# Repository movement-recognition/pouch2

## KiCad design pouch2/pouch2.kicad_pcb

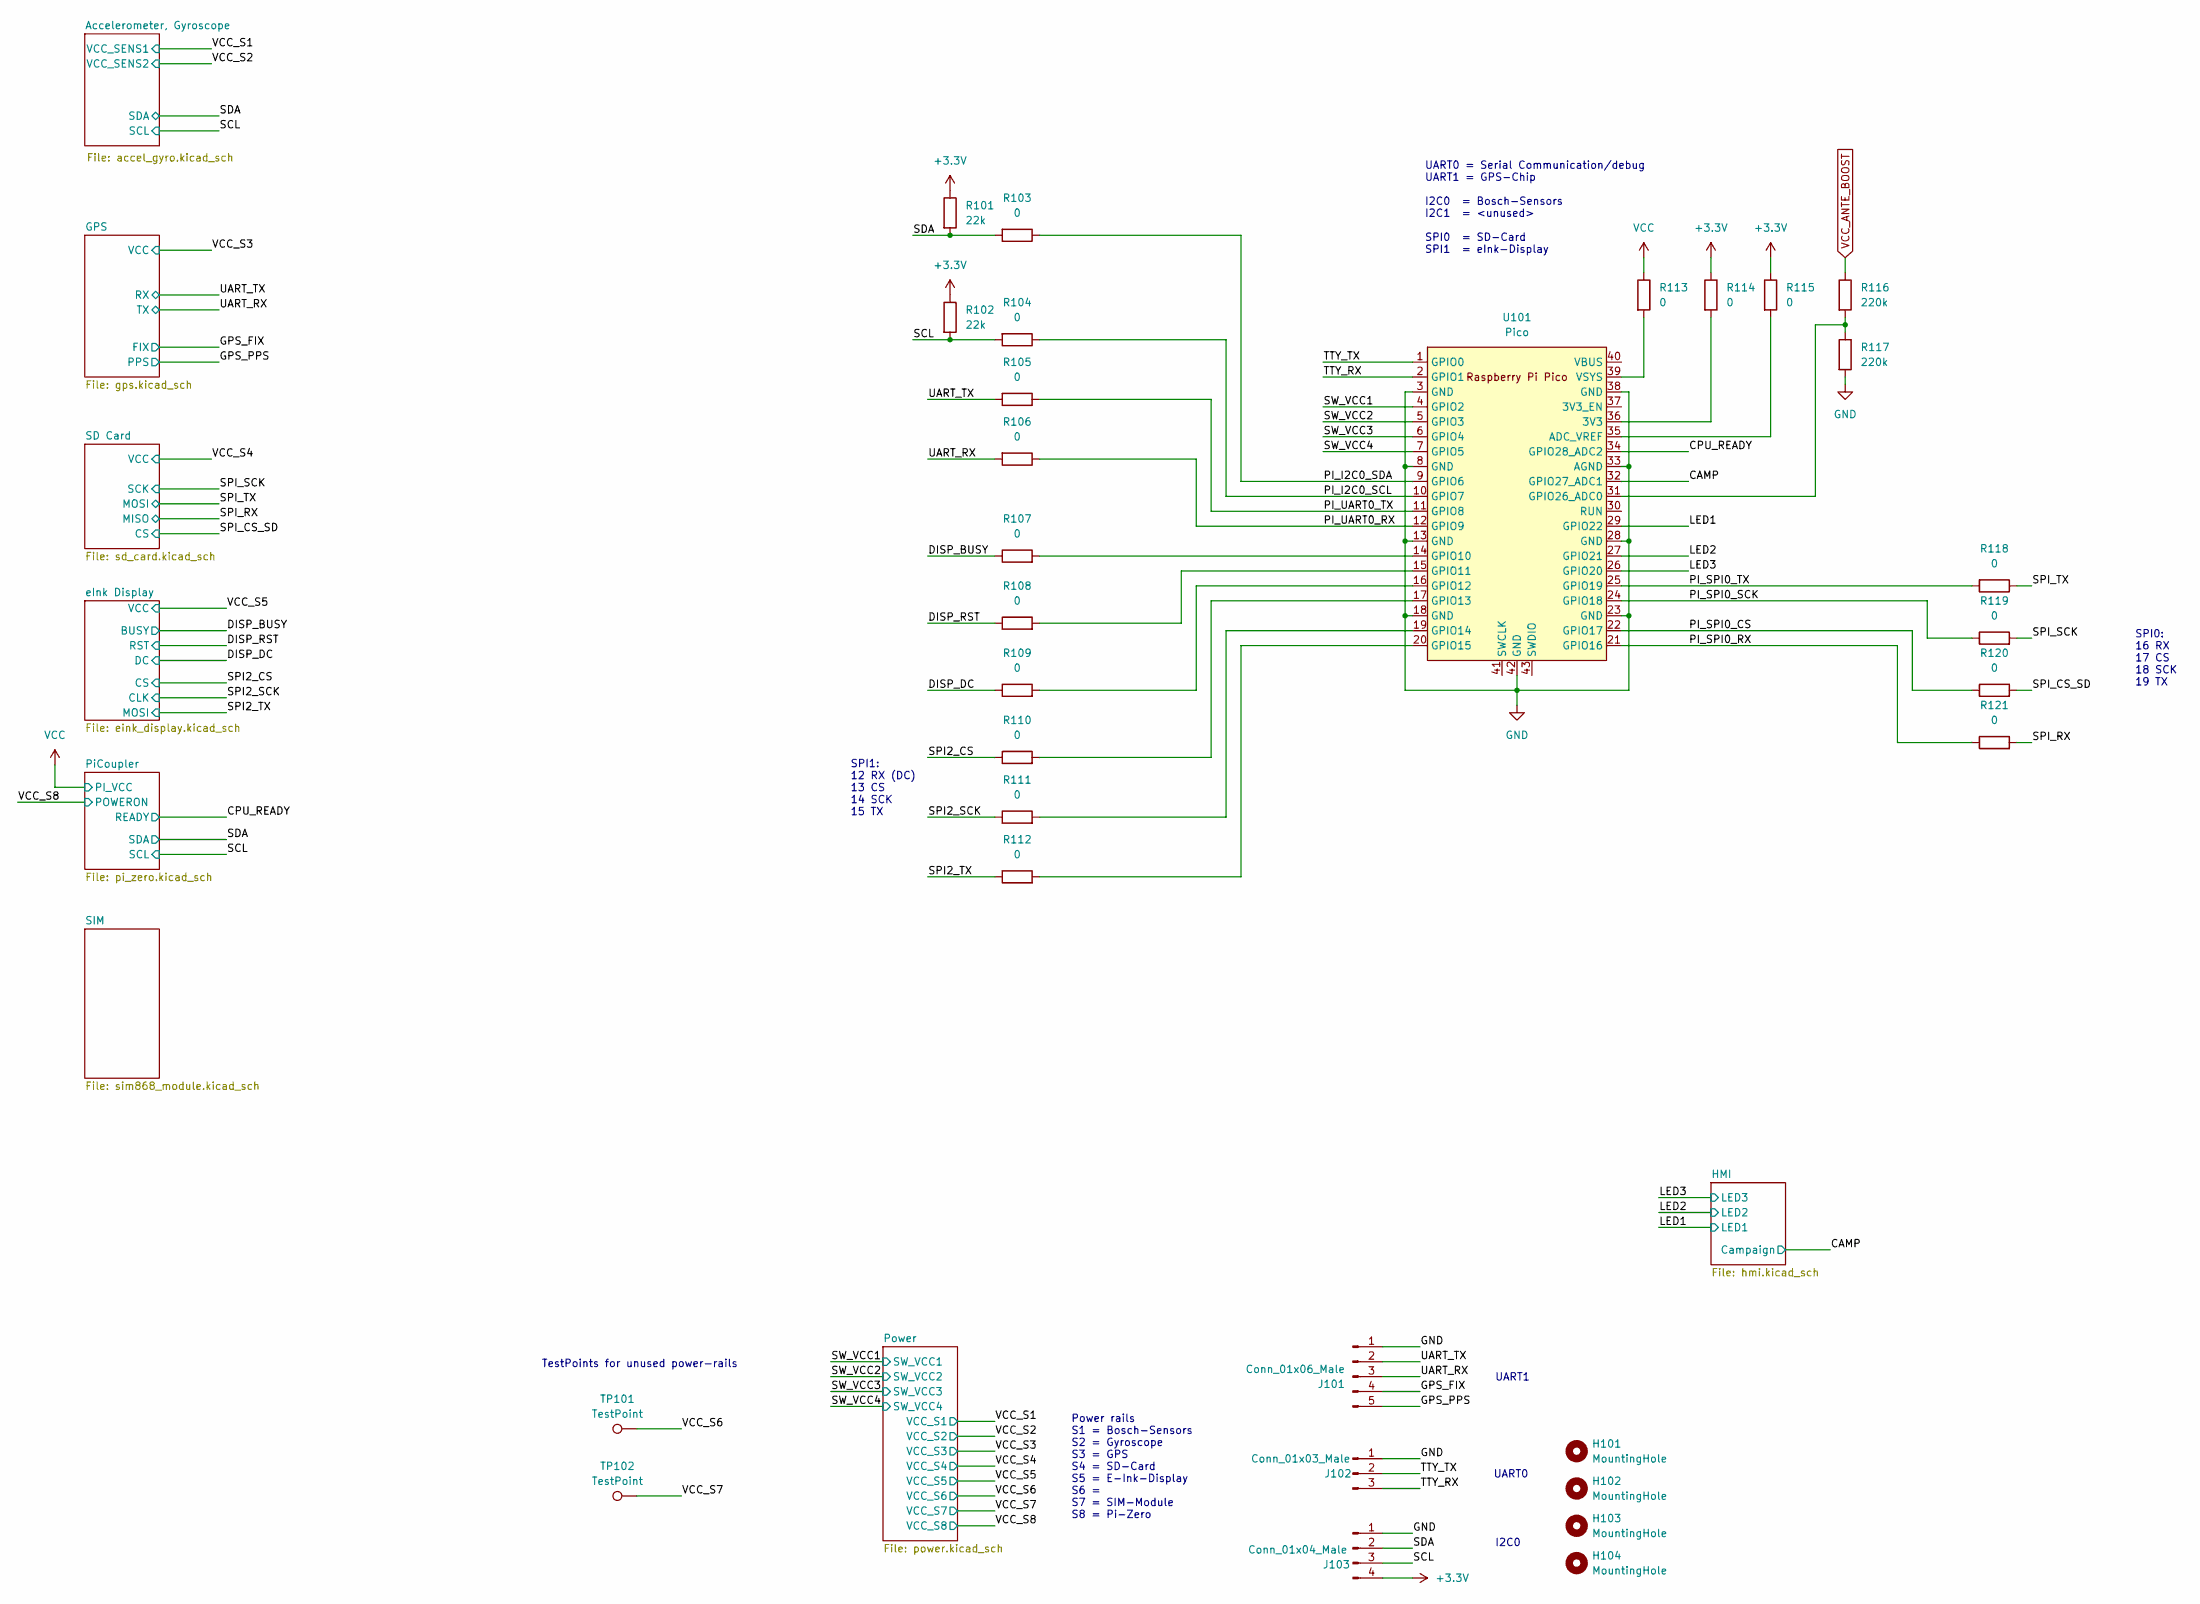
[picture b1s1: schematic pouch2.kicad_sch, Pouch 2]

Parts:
H101, H102, H103, H104: MountingHole; MountingHole_3.2mm_M3_DIN965_Pad_TopBottom
J101: Conn_01x06_Male; PinHeader_1x05_P2.54mm_Vertical
J102: Conn_01x03_Male; PinHeader_1x03_P2.54mm_Vertical
J103: Conn_01x04_Male; PinHeader_1x04_P2.54mm_Vertical
R101, R102: 22k; R_0805_2012Metric; MPN_Eurocircuit GPR080522K; LCSC C17560
R103, R104, R105, R106, R107, R108, R109, R110, R111, R112, R113, R114, R115, R118, R119, R120, R121: 0; R_0805_2012Metric; MPN_Eurocircuit GPR08050R; LCSC C17477
R116, R117: 220k; R_0805_2012Metric; MPN_Eurocircuit GPR0805220K; LCSC C17556
TP101, TP102: TestPoint; TestPoint_Pad_1.0x1.0mm
U101: Pico; RPi_Pico_SMD_TH

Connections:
+3.3V: J103.4, R101.1, R102.1, R114.1, R115.1; also elsewhere on the board
/CAMP: U101.32 (GPIO27_ADC1); also elsewhere on the board
/CPU_READY: U101.34 (GPIO28_ADC2); also elsewhere on the board
/DISP_BUSY: R107.1; also elsewhere on the board
/DISP_DC: R109.1; also elsewhere on the board
/DISP_RST: R108.1; also elsewhere on the board
/GPS_FIX: J101.4; also elsewhere on the board
/GPS_PPS: J101.5; also elsewhere on the board
/LED1: U101.29 (GPIO22); also elsewhere on the board
/LED2: U101.27 (GPIO21); also elsewhere on the board
/LED3: U101.26 (GPIO20); also elsewhere on the board
/PI_I2C0_SCL: R104.1, U101.10 (GPIO7)
/PI_I2C0_SDA: R103.1, U101.9 (GPIO6)
/PI_SPI0_CS: R120.1, U101.22 (GPIO17)
/PI_SPI0_RX: R121.1, U101.21 (GPIO16)
/PI_SPI0_SCK: R119.1, U101.24 (GPIO18)
/PI_SPI0_TX: R118.2, U101.25 (GPIO19)
/PI_UART0_RX: R106.1, U101.12 (GPIO9)
/PI_UART0_TX: R105.1, U101.11 (GPIO8)
/SCL: J103.3, R102.2, R104.2; also elsewhere on the board
/SDA: J103.2, R101.2, R103.2; also elsewhere on the board
/SPI2_CS: R110.1; also elsewhere on the board
/SPI2_SCK: R111.1; also elsewhere on the board
/SPI2_TX: R112.1; also elsewhere on the board
/SPI_CS_SD: R120.2; also elsewhere on the board
/SPI_RX: R121.2; also elsewhere on the board
/SPI_SCK: R119.2; also elsewhere on the board
/SPI_TX: R118.1; also elsewhere on the board
/SW_VCC1: U101.4 (GPIO2); also elsewhere on the board
/SW_VCC2: U101.5 (GPIO3); also elsewhere on the board
/SW_VCC3: U101.6 (GPIO4); also elsewhere on the board
/SW_VCC4: U101.7 (GPIO5); also elsewhere on the board
/TTY_RX: J102.3, U101.2 (GPIO1)
/TTY_TX: J102.2, U101.1 (GPIO0)
/UART_RX: J101.3, R106.2; also elsewhere on the board
/UART_TX: J101.2, R105.2; also elsewhere on the board
/VCC_S6: TP101.1; also elsewhere on the board
/VCC_S7: TP102.1; also elsewhere on the board
GND: J101.1, J102.1, J103.1, R117.2, U101.3 (GND), U101.8 (GND), U101.13 (GND), U101.18 (GND), U101.23 (GND), U101.28 (GND), U101.33 (AGND), U101.38 (GND), U101.42 (GND); also elsewhere on the board
unnamed: R114.2, U101.36 (3V3)
unnamed: R115.2, U101.35 (ADC_VREF)
unnamed: R107.2, U101.14 (GPIO10)
unnamed: R108.2, U101.15 (GPIO11)
unnamed: R109.2, U101.16 (GPIO12)
unnamed: R110.2, U101.17 (GPIO13)
unnamed: R111.2, U101.19 (GPIO14)
unnamed: R112.2, U101.20 (GPIO15)
unnamed: R116.2, R117.1, U101.31 (GPIO26_ADC0)
unnamed: R113.2, U101.39 (VSYS)
VCC: R113.1; also elsewhere on the board
VCC_ANTE_BOOST: R116.1; also elsewhere on the board

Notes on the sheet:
UART1
Power rails S1 = Bosch-Sensors S2 = Gyroscope S3 = GPS S4 = SD-Card S5 = E-Ink-Display S6 = S7 = SIM-Module S8 = Pi-Zero
UART0
SPI0: 16 RX 17 CS 18 SCK 19 TX
TestPoints for unused power-rails
SPI1: 12 RX (DC) 13 CS 14 SCK 15 TX
I2C0
UART0 = Serial Communication/debug UART1 = GPS-Chip I2C0 = Bosch-Sensors I2C1 = <unused> SPI0 = SD-Card SPI1 = eInk-Display

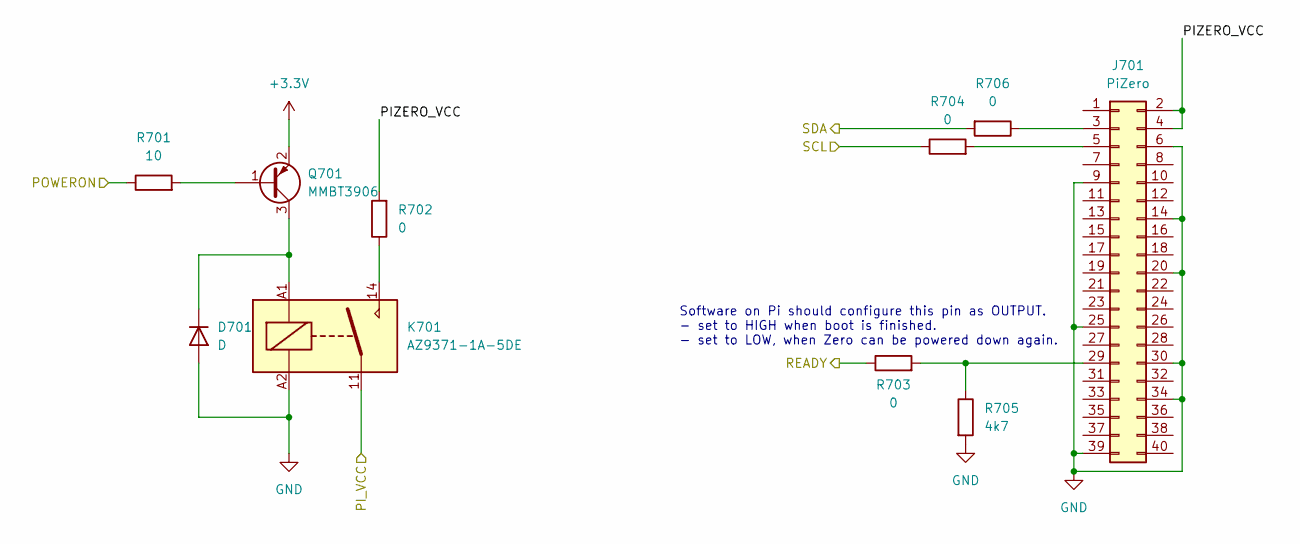
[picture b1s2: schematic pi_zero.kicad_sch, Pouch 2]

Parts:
D701: D; D_0805_2012Metric
J701: PiZero; Raspberry_Pi_Zero_Socket_wo_drills
K701: AZ9371-1A-5DE; Relay_1-Form-A_Schrack-RYII_RM5mm
Q701: MMBT3906; SOT-23; MPN_Eurocircuit MMBT3906
R701: 10; R_0805_2012Metric; MPN_Eurocircuit GPR080510R; LCSC C17415
R702, R703, R704, R706: 0; R_0805_2012Metric; MPN_Eurocircuit GPR08050R; LCSC C17477
R705: 4k7; R_0805_2012Metric; MPN_Eurocircuit GPR08054K7; LCSC C17673

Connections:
+3.3V: Q701.2 (E); also elsewhere on the board
/CPU_READY: R703.1; also elsewhere on the board
/PiCoupler/PIZERO_VCC: J701.2, J701.4, R702.2
/SCL: R704.1; also elsewhere on the board
/SDA: R706.2; also elsewhere on the board
/VCC_S8: R701.1; also elsewhere on the board
GND: D701.2 (A), J701.6, J701.9, J701.14, J701.20, J701.25, J701.30, J701.34, J701.39, K701.A2, R705.2; also elsewhere on the board
unnamed: D701.1 (K), K701.A1, Q701.3 (C)
unnamed: J701.3, R706.1
unnamed: J701.5, R704.2
unnamed: J701.29, R703.2, R705.1
unnamed: K701.14, R702.1
unnamed: Q701.1 (B), R701.2
VCC: K701.11; also elsewhere on the board

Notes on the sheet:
Software on Pi should configure this pin as OUTPUT. - set to HIGH when boot is finished. - set to LOW, when Zero can be powered down again.

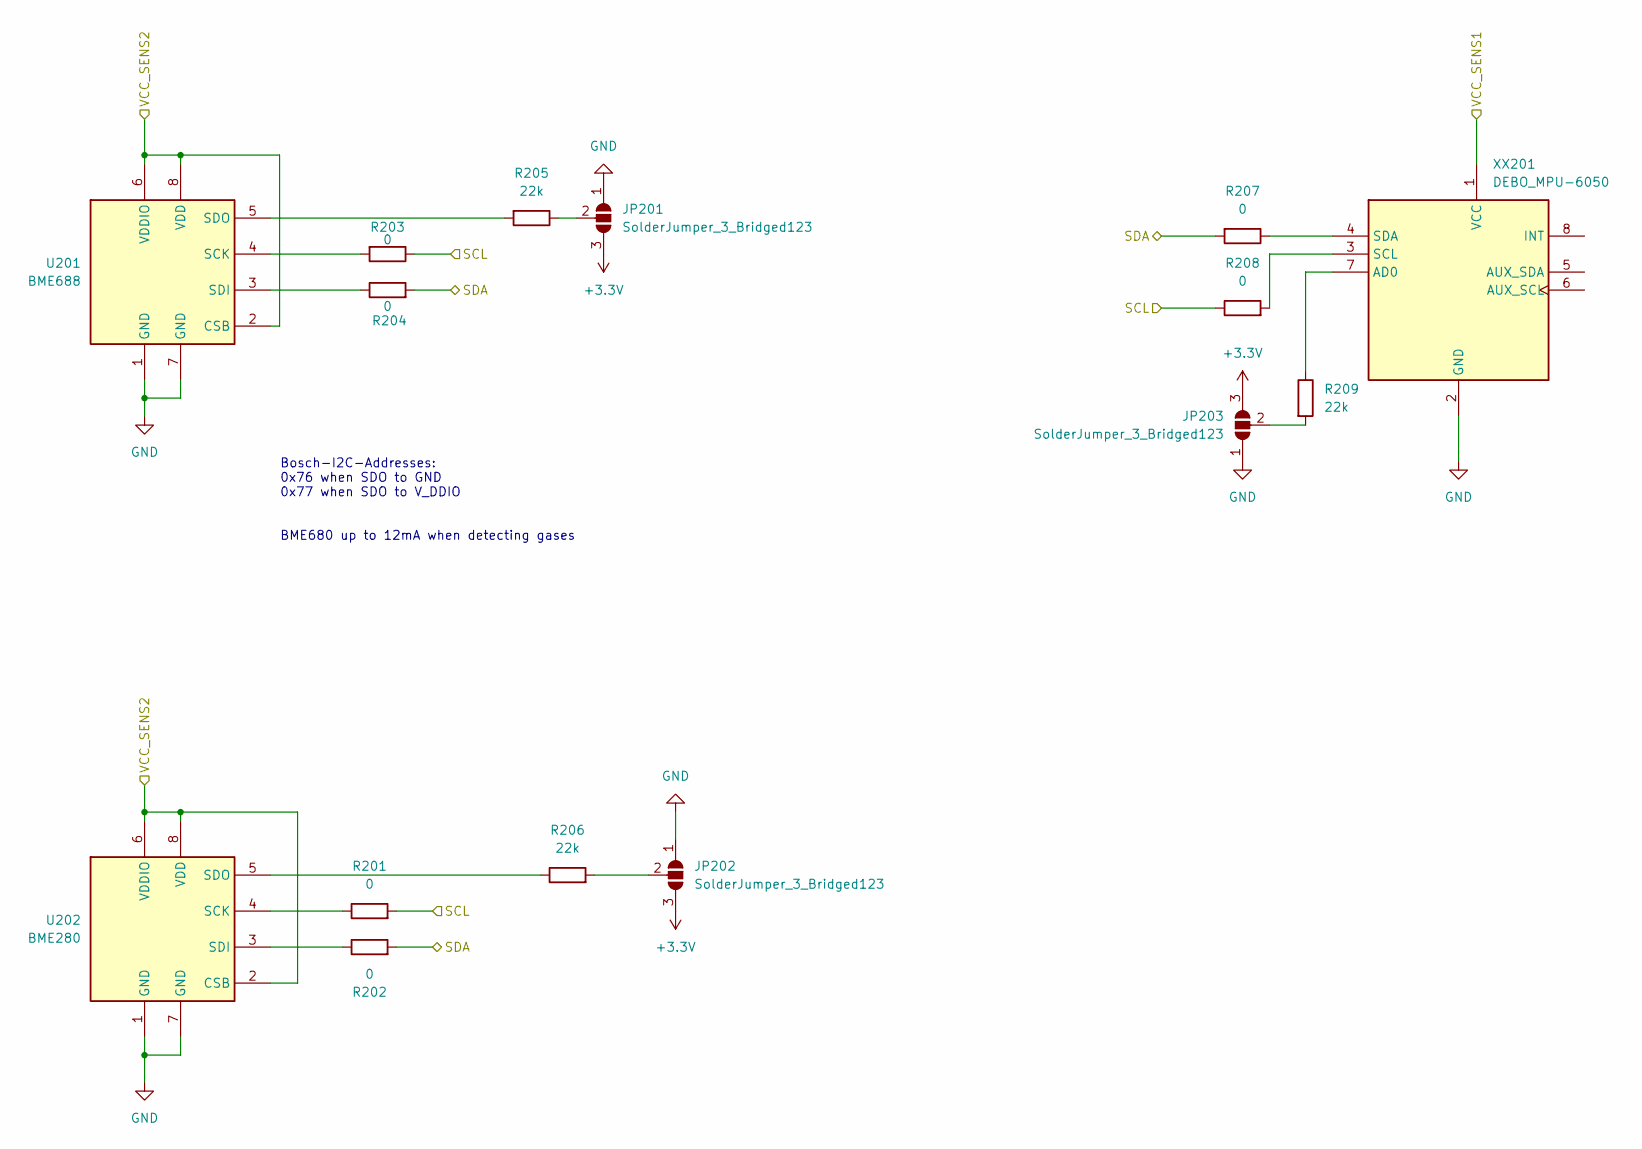
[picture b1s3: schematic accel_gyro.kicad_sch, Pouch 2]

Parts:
JP201, JP202, JP203: SolderJumper_3_Bridged123; SolderJumper-3_P2.0mm_Open_TrianglePad1.0x1.5mm_NumberLabels
R201, R202, R203, R204, R207, R208: 0; R_0805_2012Metric; MPN_Eurocircuit GPR08050R; LCSC C17477
R205, R206, R209: 22k; R_0805_2012Metric; MPN_Eurocircuit GPR080522K; LCSC C17560
U201: BME688; Bosch_LGA-8_3x3mm_P0.8mm_ClockwisePinNumbering
U202: BME280; Bosch_LGA-8_2.5x2.5mm_P0.65mm_ClockwisePinNumbering
XX201: DEBO_MPU-6050; DEBO_MPU6050

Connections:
+3.3V: JP201.3 (B), JP202.3 (B), JP203.3 (B); also elsewhere on the board
/SCL: R201.2, R203.1, R208.1; also elsewhere on the board
/SDA: R202.2, R204.2, R207.2; also elsewhere on the board
/VCC_S1: XX201.1 (VCC); also elsewhere on the board
/VCC_S2: U201.2 (CSB), U201.6 (VDDIO), U201.8 (VDD), U202.2 (CSB), U202.6 (VDDIO), U202.8 (VDD); also elsewhere on the board
GND: JP201.1 (A), JP202.1 (A), JP203.1 (A), U201.1 (GND), U201.7 (GND), U202.1 (GND), U202.7 (GND), XX201.2 (GND); also elsewhere on the board
unnamed: JP201.2 (C), R205.1
unnamed: JP202.2 (C), R206.2
unnamed: JP203.2 (C), R209.2
unnamed: R203.2, U201.4 (SCK)
unnamed: R204.1, U201.3 (SDI)
unnamed: R205.2, U201.5 (SDO)
unnamed: R201.1, U202.4 (SCK)
unnamed: R202.1, U202.3 (SDI)
unnamed: R206.1, U202.5 (SDO)
unnamed: R209.1, XX201.7 (AD0)
unnamed: R208.2, XX201.3 (SCL)
unnamed: R207.1, XX201.4 (SDA)

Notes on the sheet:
Bosch-I2C-Addresses: 0x76 when SDO to GND 0x77 when SDO to V_DDIO BME680 up to 12mA when detecting gases

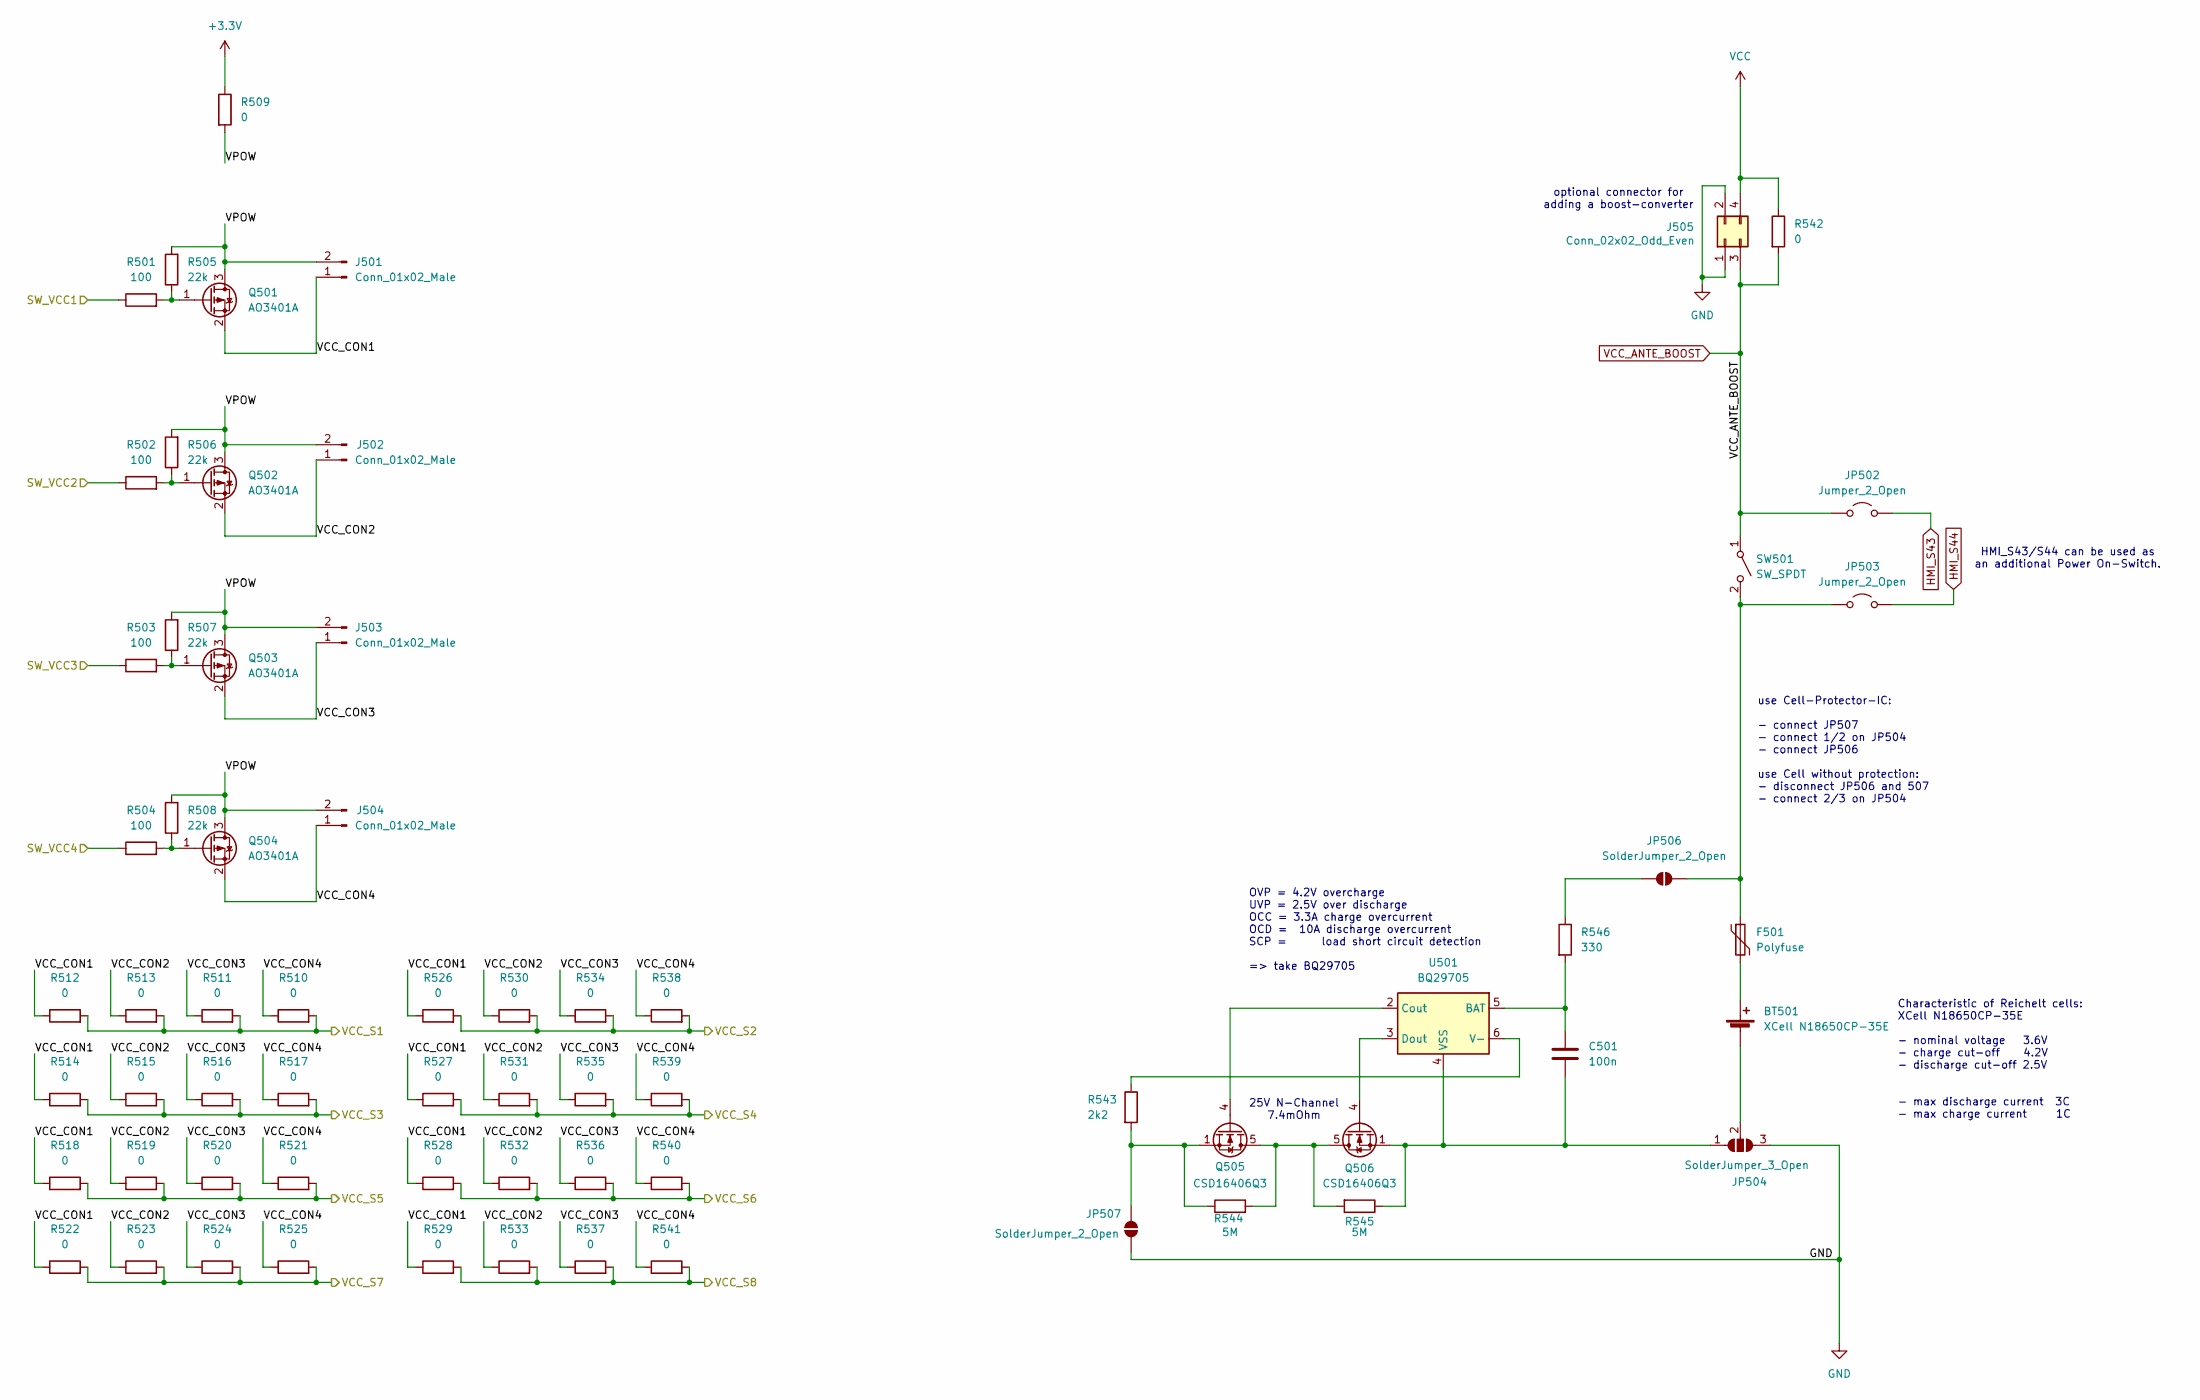
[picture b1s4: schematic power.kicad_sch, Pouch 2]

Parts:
BT501: XCell N18650CP-35E; 18650_Keystone_1043
C501: 100n; C_0805_2012Metric; MPN_Eurocircuit GPC0805104
F501: Polyfuse; Fuse_BelFuse_0ZRE0005FF_L8.3mm_W3.8mm
J501, J502, J503, J504: Conn_01x02_Male; PinHeader_1x02_P2.54mm_Vertical
J505: Conn_02x02_Odd_Even; PinHeader_1x04_P2.54mm_Vertical
JP502, JP503: Jumper_2_Open; SolderJumper-2_P1.3mm_Open_TrianglePad1.0x1.5mm
JP504: SolderJumper_3_Open; SolderJumper-3_P2.0mm_Open_TrianglePad1.0x1.5mm_NumberLabels
JP506, JP507: SolderJumper_2_Open; SolderJumper-2_P1.3mm_Open_TrianglePad1.0x1.5mm
Q501, Q502, Q503, Q504: AO3401A; SOT-23; MPN_Eurocircuit AO3401A; LCSC C15127
Q505, Q506: CSD16406Q3; VSON-8-1EP_3x3mm_P0.65mm_EP1.65x2.4mm; MPN_Eurocircuit CSD16406Q3
R501, R502, R503, R504: 100; R_0805_2012Metric; MPN_Eurocircuit GPR0805100R; LCSC C17408
R505, R506, R507, R508: 22k; R_0805_2012Metric; MPN_Eurocircuit GPR080522K; LCSC C17560
R509, R510, R511, R512, R513, R514, R515, R516, R517, R518, R519, R520, R521, R522, R523, R524, R525, R526, R527, R528, R529, R530, R531, R532, R533, R534, R535, R536, R537, R538, R539, R540, R541, R542: 0; R_0805_2012Metric; MPN_Eurocircuit GPR08050R; LCSC C17477
R543: 2k2; R_0805_2012Metric; MPN_Eurocircuit GPR08052K2; LCSC C17520
R544, R545: 5M; R_0805_2012Metric; MPN_Eurocircuit GPR08055M1; LCSC C2933370
R546: 330; R_0805_2012Metric; MPN_Eurocircuit GPR0805330R; LCSC C17630
SW501: SW_SPDT; PinHeader_1x02_P2.54mm_Vertical
U501: BQ29705; WSON-6_1.5x1.5mm_P0.5mm; MPN_Eurocircuit BQ29705DSER

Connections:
+3.3V: R509.1; also elsewhere on the board
/Power/VCC_CON1: J501.1, Q501.2 (S), R512.1, R514.1, R518.1, R522.1, R526.1, R527.1, R528.1, R529.1
/Power/VCC_CON2: J502.1, Q502.2 (S), R513.1, R515.1, R519.1, R523.1, R530.1, R531.1, R532.1, R533.1
/Power/VCC_CON3: J503.1, Q503.2 (S), R511.1, R516.1, R520.1, R524.1, R534.1, R535.1, R536.1, R537.1
/Power/VCC_CON4: J504.1, Q504.2 (S), R510.1, R517.1, R521.1, R525.1, R538.1, R539.1, R540.1, R541.1
/Power/VPOW: J501.2, J502.2, J503.2, J504.2, Q501.3 (D), Q502.3 (D), Q503.3 (D), Q504.3 (D), R505.2, R506.2, R507.2, R508.2, R509.2
/SW_VCC1: R501.1; also elsewhere on the board
/SW_VCC2: R502.1; also elsewhere on the board
/SW_VCC3: R503.1; also elsewhere on the board
/SW_VCC4: R504.1; also elsewhere on the board
/VCC_S1: R510.2, R511.2, R512.2, R513.2; also elsewhere on the board
/VCC_S2: R526.2, R530.2, R534.2, R538.2; also elsewhere on the board
/VCC_S3: R514.2, R515.2, R516.2, R517.2; also elsewhere on the board
/VCC_S4: R527.2, R531.2, R535.2, R539.2; also elsewhere on the board
/VCC_S5: R518.2, R519.2, R520.2, R521.2; also elsewhere on the board
/VCC_S6: R528.2, R532.2, R536.2, R540.2; also elsewhere on the board
/VCC_S7: R522.2, R523.2, R524.2, R525.2; also elsewhere on the board
/VCC_S8: R529.2, R533.2, R537.2, R541.2; also elsewhere on the board
GND: J505.1, J505.2, JP504.3 (B), JP507.1 (A); also elsewhere on the board
HMI_S43: JP502.2 (B); also elsewhere on the board
HMI_S44: JP503.2 (B); also elsewhere on the board
unnamed: BT501.1 (+), F501.2
unnamed: BT501.2 (-), JP504.2 (C)
unnamed: F501.1, JP503.1 (A), JP506.1 (A), SW501.2 (B)
unnamed: C501.2, JP504.1 (A), Q506.1 (S), Q506.2 (S), Q506.3 (S), R545.1, U501.4 (VSS)
unnamed: JP506.2 (B), R546.1
unnamed: JP507.2 (B), Q505.1 (S), Q505.2 (S), Q505.3 (S), R543.2, R544.1
unnamed: Q501.1 (G), R501.2, R505.1
unnamed: Q502.1 (G), R502.2, R506.1
unnamed: Q503.1 (G), R503.2, R507.1
unnamed: Q504.1 (G), R504.2, R508.1
unnamed: Q505.5 (D), Q506.5 (D), R544.2, R545.2
unnamed: Q505.4 (G), U501.2 (Cout)
unnamed: Q506.4 (G), U501.3 (Dout)
unnamed: C501.1, R546.2, U501.5 (BAT)
unnamed: R543.1, U501.6 (V-)
VCC: J505.4, R542.1; also elsewhere on the board
VCC_ANTE_BOOST: J505.3, JP502.1 (A), R542.2, SW501.1 (A); also elsewhere on the board

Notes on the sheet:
25V N-Channel 7.4mOhm
HMI_S43/S44 can be used as an additional Power On-Switch.
OVP = 4.2V overcharge UVP = 2.5V over discharge OCC = 3.3A charge overcurrent OCD = 10A discharge overcurrent SCP = load short circuit detection => take BQ29705
use Cell-Protector-IC: - connect JP507 - connect 1/2 on JP504 - connect JP506 use Cell without protection: - disconnect JP506 and 507 - connect 2/3 on JP504
optional connector for adding a boost-converter
Characteristic of Reichelt cells: XCell N18650CP-35E - nominal voltage 3.6V - charge cut-off 4.2V - discharge cut-off 2.5V - max discharge current 3C - max charge current 1C

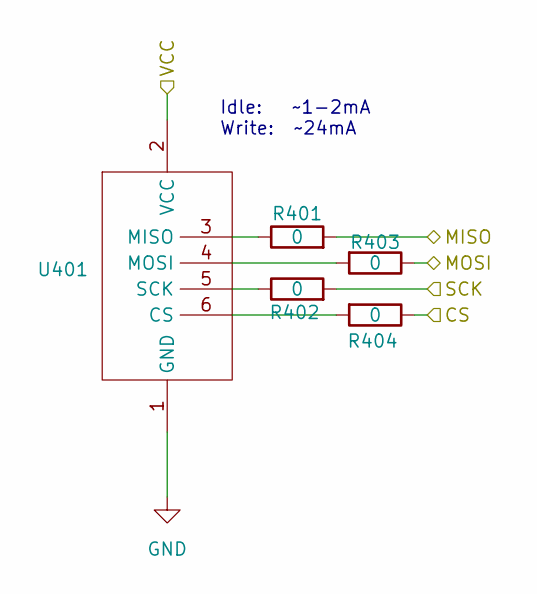
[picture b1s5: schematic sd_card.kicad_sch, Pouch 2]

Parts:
R401, R402, R403, R404: 0; R_0805_2012Metric; MPN_Eurocircuit GPR08050R; LCSC C17477
U401: DEBO_SD-Card

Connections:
/SPI_CS_SD: R404.1; also elsewhere on the board
/SPI_RX: R401.2; also elsewhere on the board
/SPI_SCK: R402.2; also elsewhere on the board
/SPI_TX: R403.1; also elsewhere on the board
/VCC_S4: U401.2 (VCC); also elsewhere on the board
GND: U401.1 (GND); also elsewhere on the board
unnamed: R404.2, U401.6 (CS)
unnamed: R401.1, U401.3 (MISO)
unnamed: R403.2, U401.4 (MOSI)
unnamed: R402.1, U401.5 (SCK)

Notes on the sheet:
Idle: ~1-2mA Write: ~24mA

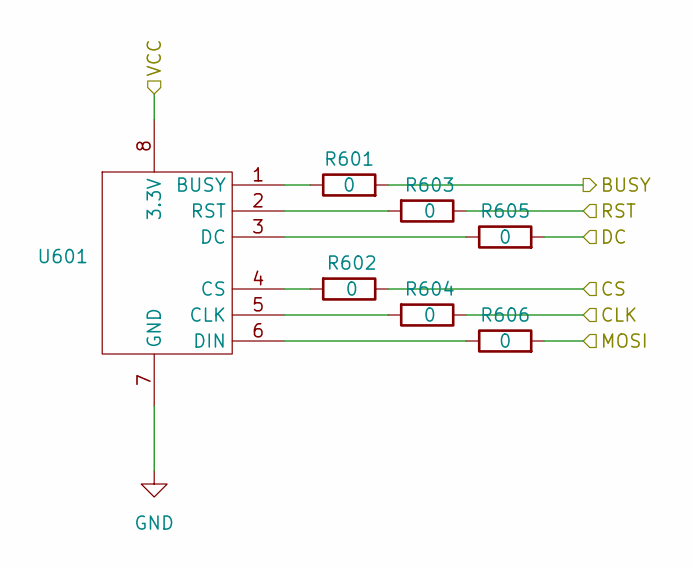
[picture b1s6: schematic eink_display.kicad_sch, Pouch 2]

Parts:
R601, R602, R603, R604, R605, R606: 0; R_0805_2012Metric; MPN_Eurocircuit GPR08050R; LCSC C17477
U601: PinHeader_1x08_P2.54mm_Vertical

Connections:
/DISP_BUSY: R601.2; also elsewhere on the board
/DISP_DC: R605.2; also elsewhere on the board
/DISP_RST: R603.1; also elsewhere on the board
/SPI2_CS: R602.1; also elsewhere on the board
/SPI2_SCK: R604.1; also elsewhere on the board
/SPI2_TX: R606.2; also elsewhere on the board
/VCC_S5: U601.8 (3.3V); also elsewhere on the board
GND: U601.7 (GND); also elsewhere on the board
unnamed: R601.1, U601.1 (BUSY)
unnamed: R604.2, U601.5 (CLK)
unnamed: R602.2, U601.4 (CS)
unnamed: R605.1, U601.3 (DC)
unnamed: R606.1, U601.6 (DIN)
unnamed: R603.2, U601.2 (RST)

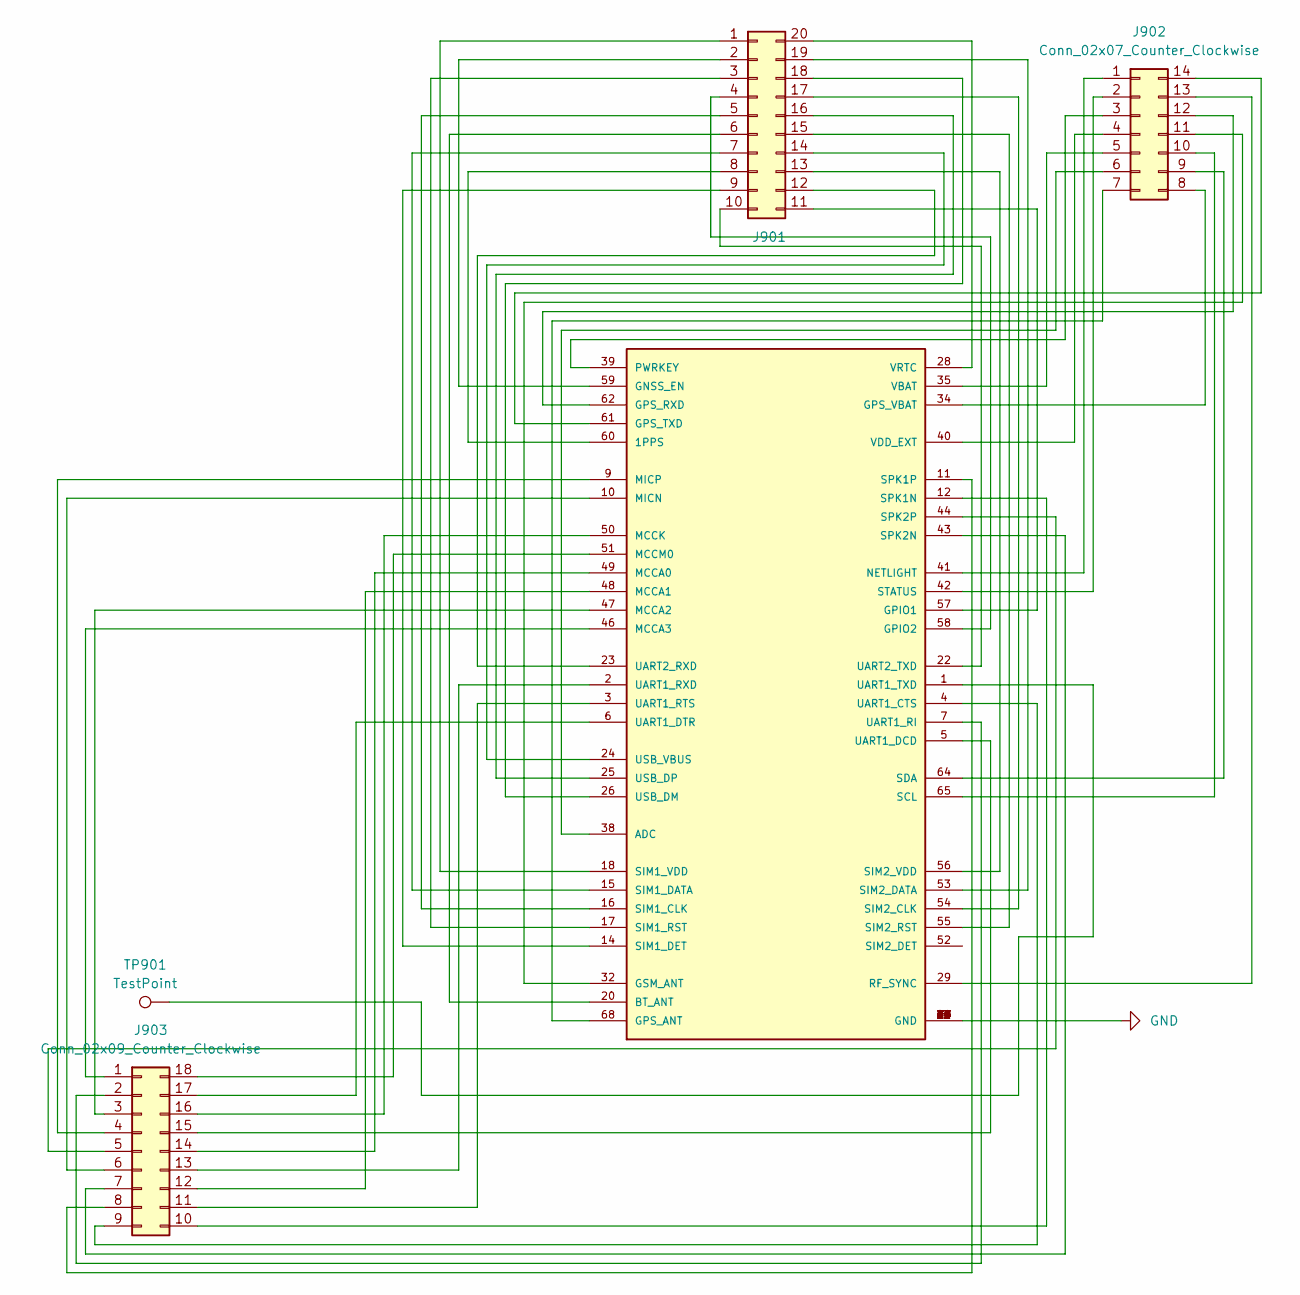
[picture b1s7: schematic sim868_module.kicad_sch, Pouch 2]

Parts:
J901: Conn_02x03_Counter_Clockwise; PinHeader_2x10_P1.00mm_Vertical_SMD
J902: Conn_02x07_Counter_Clockwise; PinHeader_2x07_P1.00mm_Vertical_SMD
J903: Conn_02x09_Counter_Clockwise; PinHeader_2x09_P1.00mm_Vertical_SMD
TP901: TestPoint; TestPoint_Pad_D1.0mm
U901: SIM868; XCVR_SIM868

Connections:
GND: U901.8 (GND), U901.13 (GND), U901.19 (GND), U901.21 (GND), U901.27 (GND), U901.30 (GND), U901.31 (GND), U901.33 (GND), U901.36 (GND), U901.37 (GND), U901.45 (GND), U901.63 (GND), U901.66 (GND), U901.67 (GND), U901.69 (GND), U901.70 (GND), U901.71 (GND), U901.72 (GND), U901.73 (GND), U901.74 (GND), U901.75 (GND), U901.76 (GND), U901.77 (GND); also elsewhere on the board
unnamed: J901.1, U901.18 (SIM1_VDD)
unnamed: J901.2, U901.59 (GNSS_EN)
unnamed: J901.3, U901.17 (SIM1_RST)
unnamed: J901.4, U901.58 (GPIO2)
unnamed: J901.5, U901.16 (SIM1_CLK)
unnamed: J901.6, U901.20 (BT_ANT)
unnamed: J901.7, U901.15 (SIM1_DATA)
unnamed: J901.8, U901.60 (1PPS)
unnamed: J901.9, U901.14 (SIM1_DET)
unnamed: J901.10, U901.22 (UART2_TXD)
unnamed: J901.11, U901.57 (GPIO1)
unnamed: J901.12, U901.23 (UART2_RXD)
unnamed: J901.13, U901.56 (SIM2_VDD)
unnamed: J901.14, U901.24 (USB_VBUS)
unnamed: J901.15, U901.55 (SIM2_RST)
unnamed: J901.16, U901.25 (USB_DP)
unnamed: J901.17, U901.54 (SIM2_CLK)
unnamed: J901.18, U901.26 (USB_DM)
unnamed: J901.19, U901.53 (SIM2_DATA)
unnamed: J901.20, U901.28 (VRTC)
unnamed: J902.1, U901.41 (NETLIGHT)
unnamed: J902.2, U901.42 (STATUS)
unnamed: J902.3, U901.39 (PWRKEY)
unnamed: J902.4, U901.40 (VDD_EXT)
unnamed: J902.5, U901.35 (VBAT)
unnamed: J902.6, U901.38 (ADC)
unnamed: J902.7, U901.68 (GPS_ANT)
unnamed: J902.8, U901.34 (GPS_VBAT)
unnamed: J902.9, U901.64 (SDA)
unnamed: J902.10, U901.65 (SCL)
unnamed: J902.11, U901.32 (GSM_ANT)
unnamed: J902.12, U901.62 (GPS_RXD)
unnamed: J902.13, U901.29 (RF_SYNC)
unnamed: J902.14, U901.61 (GPS_TXD)
unnamed: J903.1, U901.46 (MCCA3)
unnamed: J903.2, U901.7 (UART1_RI)
unnamed: J903.3, U901.47 (MCCA2)
unnamed: J903.4, U901.9 (MICP)
unnamed: J903.5, U901.44 (SPK2P)
unnamed: J903.6, U901.10 (MICN)
unnamed: J903.7, U901.43 (SPK2N)
unnamed: J903.8, U901.11 (SPK1P)
unnamed: J903.9, U901.4 (UART1_CTS)
unnamed: J903.10, U901.12 (SPK1N)
unnamed: J903.11, U901.3 (UART1_RTS)
unnamed: J903.12, U901.48 (MCCA1)
unnamed: J903.13, U901.2 (UART1_RXD)
unnamed: J903.14, U901.49 (MCCA0)
unnamed: J903.15, U901.5 (UART1_DCD)
unnamed: J903.16, U901.50 (MCCK)
unnamed: J903.17, U901.6 (UART1_DTR)
unnamed: J903.18, U901.51 (MCCM0)
unnamed: TP901.1, U901.1 (UART1_TXD)

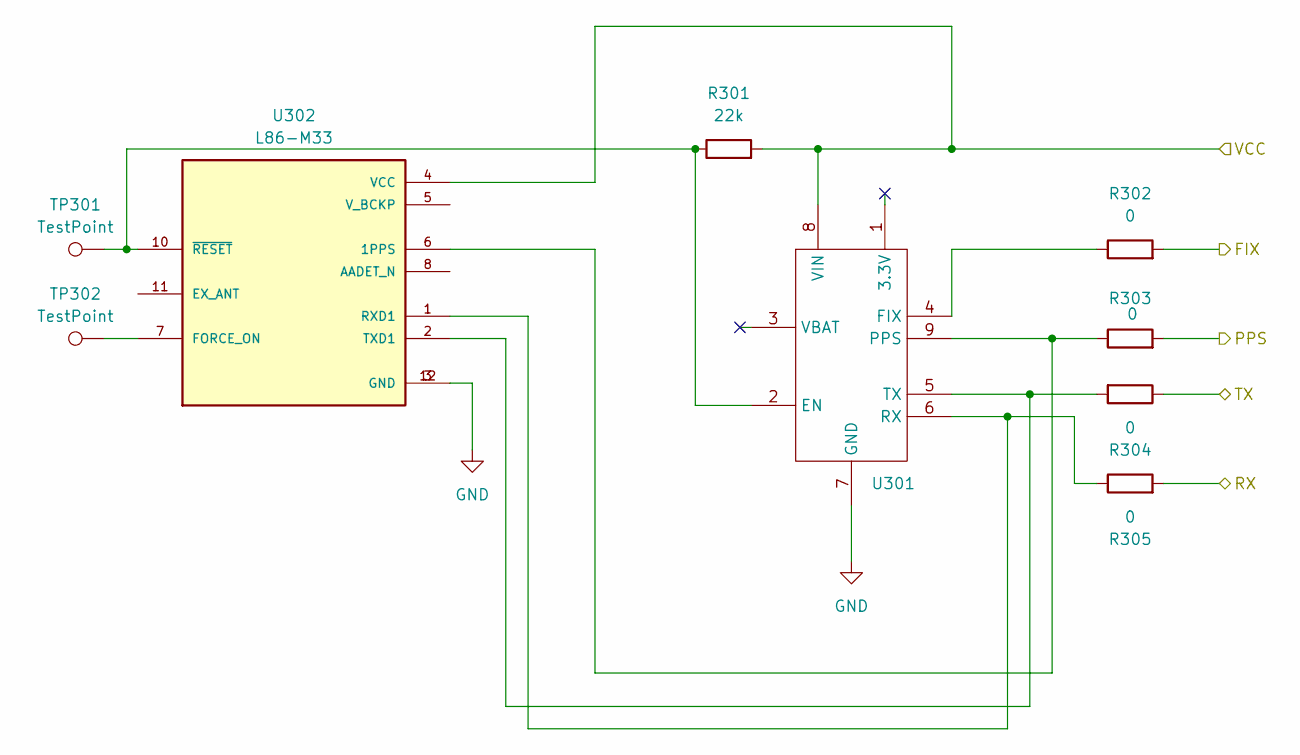
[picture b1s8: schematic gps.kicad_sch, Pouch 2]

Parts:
R301: 22k; R_0805_2012Metric; MPN_Eurocircuit GPR080522K; LCSC C17560
R302, R303, R304, R305: 0; R_0805_2012Metric; MPN_Eurocircuit GPR08050R; LCSC C17477
TP301, TP302: TestPoint; TestPoint_Pad_1.0x1.0mm
U301: DEBO_GPS
U302: L86-M33; XCVR_L86-M33

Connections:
/GPS_FIX: R302.2; also elsewhere on the board
/GPS_PPS: R303.2; also elsewhere on the board
/UART_RX: R304.1; also elsewhere on the board
/UART_TX: R305.2; also elsewhere on the board
/VCC_S3: R301.2, U301.8 (VIN), U302.4 (VCC); also elsewhere on the board
GND: U301.7 (GND), U302.3 (GND), U302.12 (GND); also elsewhere on the board
unnamed: R301.1, TP301.1, U301.2 (EN), U302.10 (~RESET)
unnamed: R302.1, U301.4 (FIX)
unnamed: R303.1, U301.9 (PPS), U302.6 (1PPS)
unnamed: R305.1, U301.6 (RX), U302.1 (RXD1)
unnamed: R304.2, U301.5 (TX), U302.2 (TXD1)
unnamed: TP302.1, U302.7 (FORCE_ON)

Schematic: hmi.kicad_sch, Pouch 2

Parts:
D801, D802, D803: LED; LED_D5.0mm
R801, R802, R803: 330; R_0805_2012Metric; MPN_Eurocircuit GPR0805330R; LCSC C17630
R804: 82k; R_0805_2012Metric; MPN_Eurocircuit GPR080582K; LCSC C17840
R805: 47k; R_0805_2012Metric; MPN_Eurocircuit GPR080547K; LCSC C17713
R806: 22k; R_0805_2012Metric; MPN_Eurocircuit GPR080522K; LCSC C17560
R807, R808: 10k; R_0805_2012Metric; MPN_Eurocircuit GPR080510K; LCSC C17414
R809: 0; R_0805_2012Metric; MPN_Eurocircuit GPR08050R; LCSC C17477
SW801: SW_DIP_x08; SW_DIP_SPSTx08_Slide_9.78x22.5mm_W7.62mm_P2.54mm

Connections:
+3.3V: SW801.1, SW801.2, SW801.3, SW801.4; also elsewhere on the board
/CAMP: R809.2; also elsewhere on the board
/LED1: R801.1; also elsewhere on the board
/LED2: R802.1; also elsewhere on the board
/LED3: R803.1; also elsewhere on the board
GND: D801.1 (K), D802.1 (K), D803.1 (K), R808.2; also elsewhere on the board
HMI_S13: SW801.5
HMI_S14: SW801.12
HMI_S23: SW801.6
HMI_S24: SW801.11
HMI_S33: SW801.7
HMI_S34: SW801.10
HMI_S43: SW801.8; also elsewhere on the board
HMI_S44: SW801.9; also elsewhere on the board
unnamed: D801.2 (A), R801.2
unnamed: D802.2 (A), R802.2
unnamed: D803.2 (A), R803.2
unnamed: R804.1, SW801.16
unnamed: R804.2, R805.2, R806.2, R807.2, R808.1, R809.1
unnamed: R805.1, SW801.15
unnamed: R806.1, SW801.14
unnamed: R807.1, SW801.13
